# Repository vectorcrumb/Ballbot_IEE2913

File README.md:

# IEE2913
Codigo, esquematicos y planos para proyecto Ballbot para el ramo IEE2913, Diseño Electrico, semestre 2019-2

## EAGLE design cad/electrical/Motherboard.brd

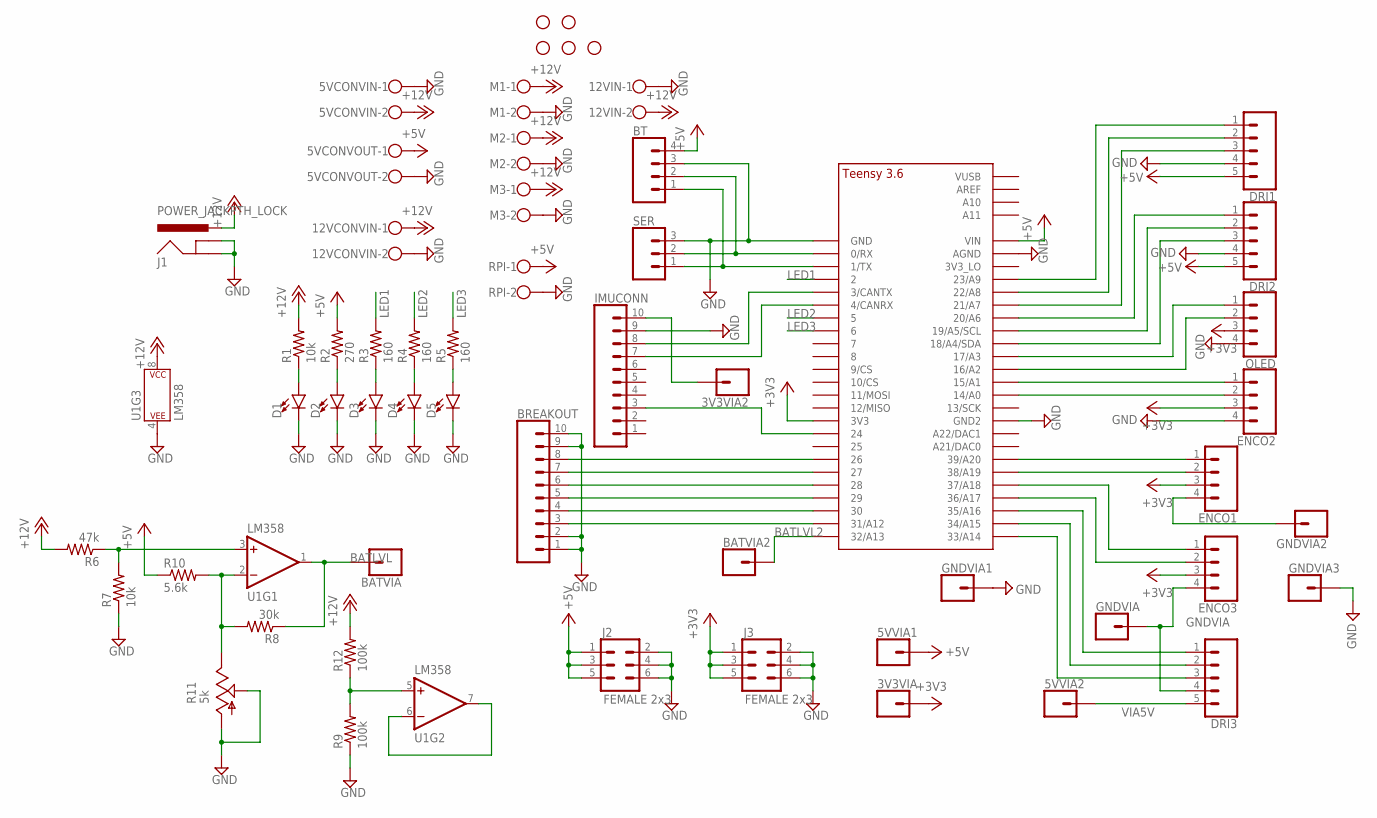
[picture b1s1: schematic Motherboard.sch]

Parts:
3V3VIA, 3V3VIA2, 5VVIA1, 5VVIA2: CONN_01; 1X01
5VCONVIN, 5VCONVOUT, 12VCONVIN, 12VIN: W237-102
BATVIA, BATVIA2: CONN_01; 1X01
BREAKOUT: CONN_10LOCK; 1X10_LOCK
BT: CONN_04LOCK; 1X04_LOCK
D1, D2, D3, D4, D5: LED5MM-KIT; LED_5MM-KIT
DRI1, DRI2, DRI3: CONN_05LOCK; 1X05_LOCK
ENCO1, ENCO2, ENCO3: CONN_04LOCK; 1X04_LOCK
GNDVIA, GNDVIA1, GNDVIA2, GNDVIA3: CONN_01; 1X01
H1, H2, H4, H5, H6: STAND-OFF
IMUCONN: CONN_10LOCK; 1X10_LOCK
J1: POWER_JACKPTH_LOCK; POWER_JACK_PTH_LOCK
J2, J3: FEMALE 2x3; 2X3
M1, M2, M3: W237-102
OLED: CONN_04LOCK; 1X04_LOCK
R1, R7: 10k; 0207/10
R2: 270; 0207/10
R3, R4, R5: 160; 0207/10
R6: 47k; 0207/10
R8: 30k; 0207/10
R9, R12: 100k; 0207/10
R10: 5.6k; 0207/10
R11: 5k; B25P
RPI: W237-102
SER: CONN_03LOCK; 1X03_LOCK
U1: LM358; DIP08
U$1: TEENSY_3.5/3.6_BASIC

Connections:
+3V3: 3V3VIA.1, ENCO1.3, ENCO2.3, ENCO3.3, J3.1, J3.3, J3.5, OLED.3, U$1.3V3
+5V: 5VCONVOUT.1, 5VVIA1.1, BT.4, DRI1.5, DRI2.5, J2.1, J2.3, J2.5, R2.2, R10.1, RPI.1, U$1.VIN
+12V: 5VCONVIN.2, 12VCONVIN.1, 12VIN.2, J1.PWR, M1.1, M2.1, M3.1, R1.2, R6.2, R12.2, U1.8 (P$V+)
BATLVL: BATVIA.1, R8.1, U1.1 (OUT)
BATLVL2: BATVIA2.1, U$1.32/A13
GND: 5VCONVIN.1, 5VCONVOUT.2, 12VCONVIN.2, 12VIN.1, BREAKOUT.1, BREAKOUT.2, BREAKOUT.9, BREAKOUT.10, BT.3, D1.K (C), D2.K (C), D3.K (C), D4.K (C), D5.K (C), DRI1.4, DRI2.4, ENCO2.4, GNDVIA1.1, GNDVIA3.1, IMUCONN.9, J1.GND, J1.GNDBREAK, J2.2, J2.4, J2.6, J3.2, J3.4, J3.6, M1.2, M2.2, M3.2, OLED.4, R7.1, R9.1, R11.A, R11.S, RPI.2, SER.3, U1.4 (P$V-), U$1.AGND, U$1.GND, U$1.GND2
GNDVIA: DRI3.4, ENCO3.4, GNDVIA.1
LED1: R3.2, U$1.2
LED2: R4.2, U$1.5
LED3: R5.2, U$1.6
unnamed: DRI1.1, U$1.23/A9
unnamed: DRI1.2, U$1.22/A8
unnamed: DRI1.3, U$1.21/A7
unnamed: DRI2.3, U$1.18/A4/SDA
unnamed: DRI2.2, U$1.19/A5/SCL
unnamed: DRI2.1, U$1.20/A6
unnamed: ENCO2.1, U$1.15/A1
unnamed: ENCO2.2, U$1.14/A0
unnamed: ENCO1.1, U$1.39/A20
unnamed: ENCO1.2, U$1.38/A19
unnamed: ENCO3.1, U$1.37/A18
unnamed: ENCO3.2, U$1.36/A17
unnamed: DRI3.1, U$1.35/A16
unnamed: DRI3.2, U$1.34/A15
unnamed: DRI3.3, U$1.33/A14
unnamed: BT.1, SER.1, U$1.1/TX
unnamed: BT.2, SER.2, U$1.0/RX
unnamed: IMUCONN.8, U$1.3/CANTX
unnamed: IMUCONN.7, U$1.4/CANRX
unnamed: IMUCONN.3, U$1.24
unnamed: R9.2, R12.1, U1.5 (+IN)
unnamed: BREAKOUT.3, U$1.31/A12
unnamed: BREAKOUT.4, U$1.30
unnamed: BREAKOUT.5, U$1.29
unnamed: BREAKOUT.6, U$1.28
unnamed: BREAKOUT.7, U$1.27
unnamed: BREAKOUT.8, U$1.26
unnamed: D2.A, R2.1
unnamed: D1.A, R1.1
unnamed: D3.A, R3.1
unnamed: D5.A, R5.1
unnamed: D4.A, R4.1
unnamed: 3V3VIA2.1, IMUCONN.10
unnamed: OLED.1, U$1.17/A3
unnamed: OLED.2, U$1.16/A2
unnamed: R6.1, R7.2, U1.3 (+IN)
unnamed: U1.6 (-IN), U1.7 (OUT)
unnamed: R8.2, R10.2, R11.E, U1.2 (-IN)
unnamed: ENCO1.4, GNDVIA2.1
VIA5V: 5VVIA2.1, DRI3.5

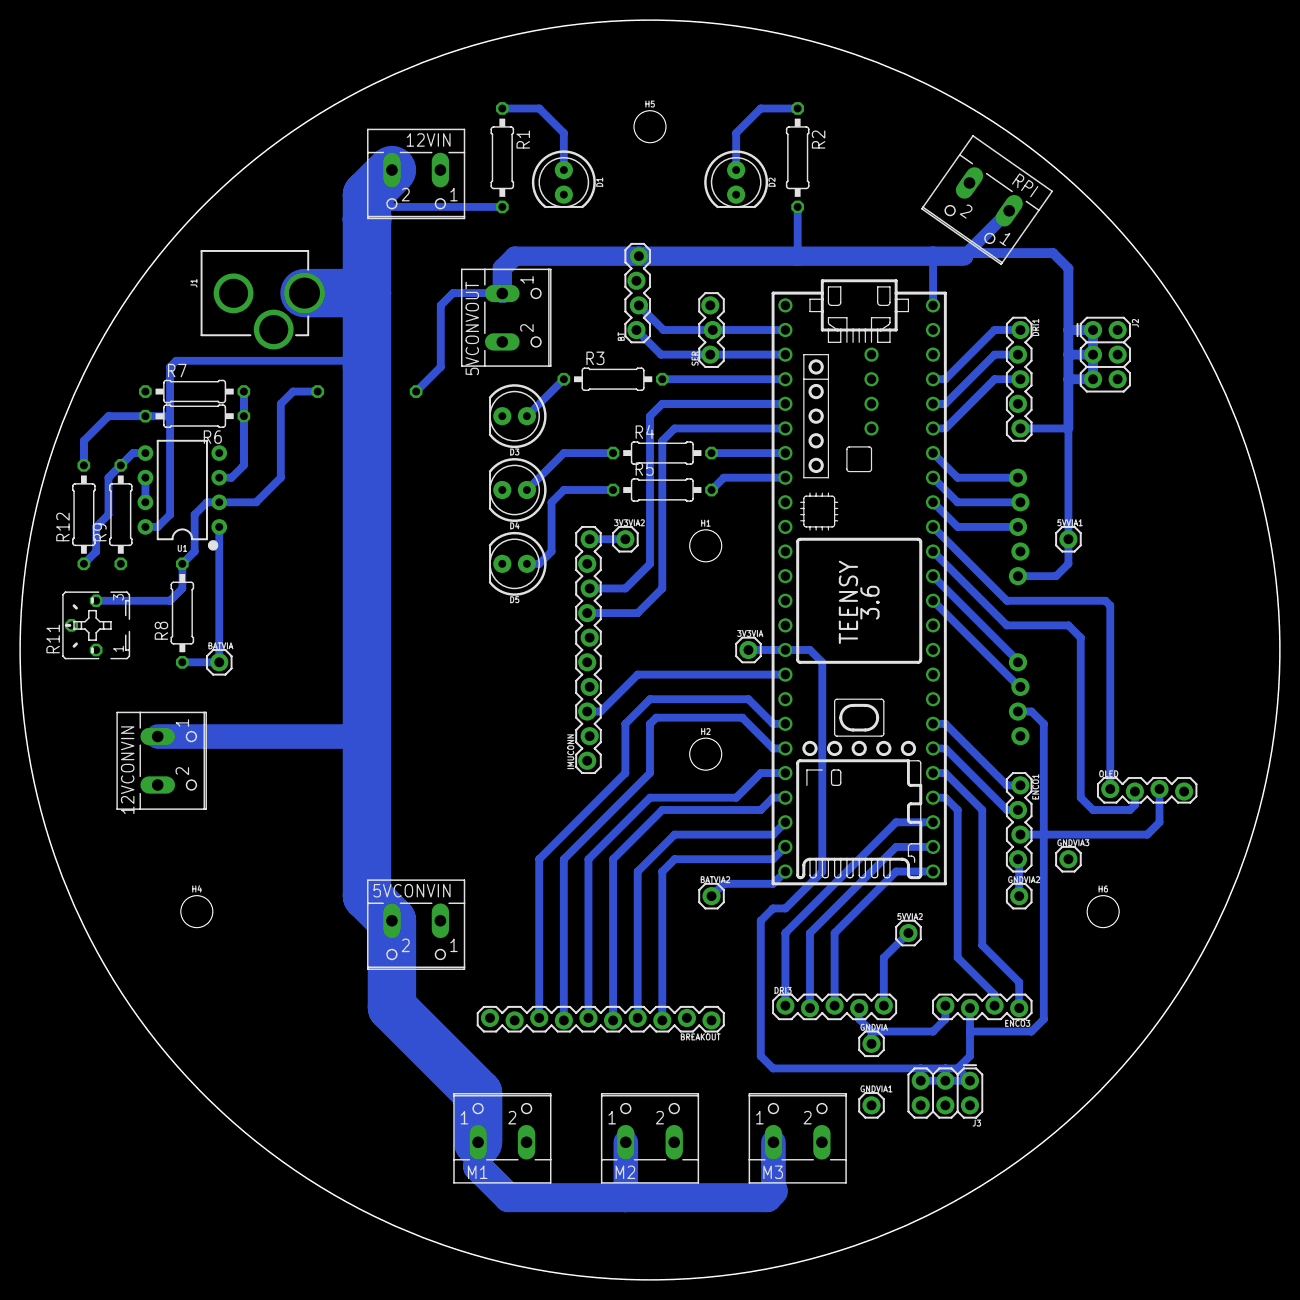
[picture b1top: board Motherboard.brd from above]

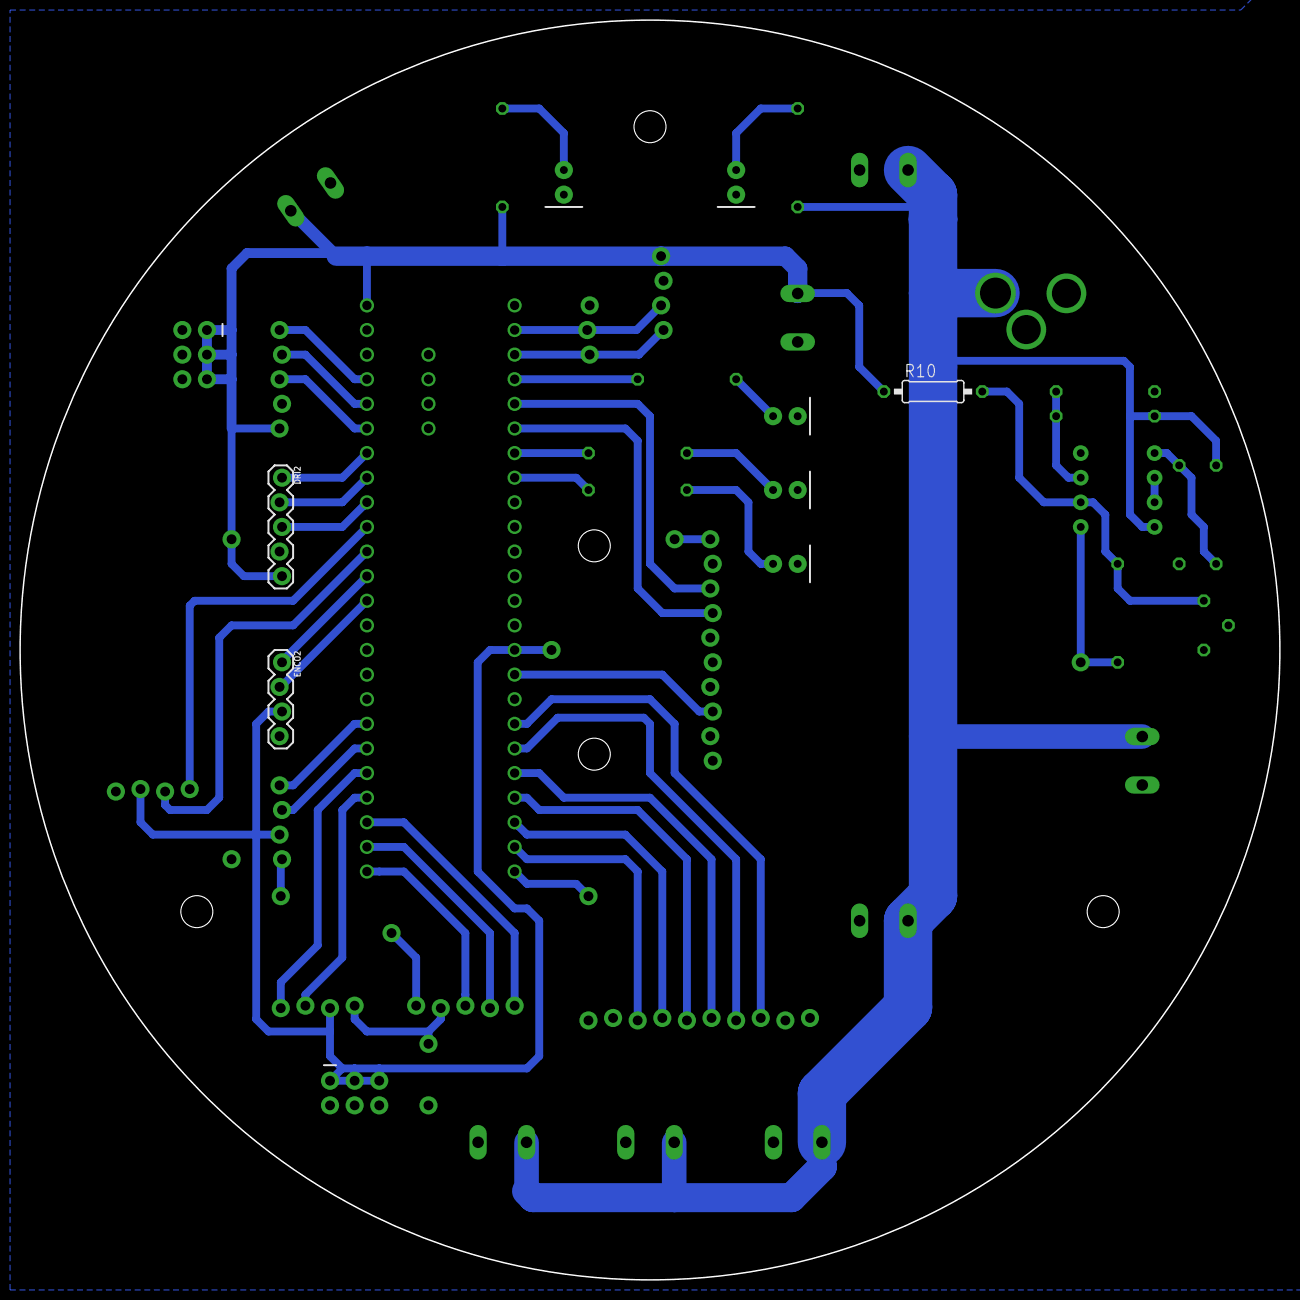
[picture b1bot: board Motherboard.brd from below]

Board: 2 copper layers, 130.0 x 130.0 mm, 56 parts (3 on the bottom side), 50 nets.

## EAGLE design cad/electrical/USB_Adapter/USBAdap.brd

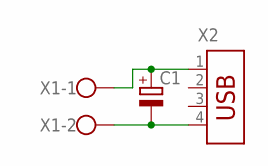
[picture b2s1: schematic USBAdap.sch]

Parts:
C1: CPOL-EUE5-8.5; E5-8,5
X1: W237-102
X2: USB-787616; USB

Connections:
unnamed: C1.+, X1.1, X2.1
unnamed: C1.-, X1.2, X2.4

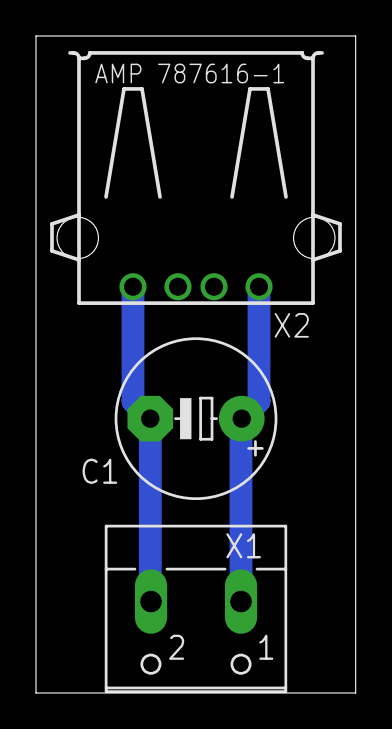
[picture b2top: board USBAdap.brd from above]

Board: 2 copper layers, 17.8 x 36.5 mm, 3 parts (0 on the bottom side), 2 nets.

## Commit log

2019-10-09 Added robot basic code and electrical CAD
2019-10-10 Imported robot code and electrical CAD
2019-10-11 Implemented MPU9250 w/Madgwick filter and OLED.
2019-10-12 Added more OLED funcionality. Modified pinout.
2019-10-12 Modded gitignore.
2019-10-12 Removed config files.
2019-10-12 Modded main, deleted makefile.
2019-10-12 Removed makefile commit, modded main.cpp.
2019-10-13 COdigo motores
2019-10-16 Added base web interface.
2019-11-03 Working plots on UI, added PJON lib, began refactoring
2019-11-03 Removed tracking on Makefile
2019-11-07 Complete robot code refactoring. Added TeensyDelay library. Still have to fix errors for TorqueMotor class.
2019-11-14 Added torque control motor.
2019-11-15 Fixed startup errors for rewrite.
2019-11-15 Fixing motor PID issues.
2019-11-15 Continued debugging. Found error in sensor reading
2019-12-03 Ultima entrega funcional
2019-12-03 Placed IMU in functions.
2019-12-03 PID lib
2019-12-04 Working PI not tuned
2019-12-09 PID tuning and torque sign
2019-12-11 11/Dic
2019-12-13 Nothing
2019-12-14 PID Torque funcionando.
2019-12-15 Reworked PID and stuff. Have to test.
2019-12-16 Fixed makefile
2019-12-16 Low pass filter
2019-12-17 Working current sensors. Motor PI wrong.
2019-12-17 Added eigen and moving average.
2019-12-18 LQR discrete constants
2019-12-18 Working PI controller on 3 motors.
2019-12-18 Reintegrated IMU. Variable offsets in readings.
2019-12-18 Added DMP library for test.
2019-12-18 Dropped DMP, added changes.
2019-12-18 Working IMU calibration
2019-12-19 Working robot code. Have to tune and add Kalman.
2019-12-19 Tuning LQR
2019-12-19 Version Presentacion Final.
2019-12-23 Working Kalman.
2022-06-21 Bump numpy from 1.16.4 to 1.22.0 in /code/app/web
    Bumps [numpy](https://github.com/numpy/numpy) from 1.16.4 to 1.22.0.
    - [Release notes](https://github.com/numpy/numpy/releases)
    - [Changelog](https://github.com/numpy/numpy/blob/main/doc/HOWTO_RELEASE.rst)
    - [Commits](https://github.com/numpy/numpy/compare/v1.16.4...v1.22.0)
    ---
    updated-dependencies:
2023-05-01 Bump flask from 1.0.2 to 2.3.2 in /code/app/web
    Bumps [flask](https://github.com/pallets/flask) from 1.0.2 to 2.3.2.
    - [Release notes](https://github.com/pallets/flask/releases)
    - [Changelog](https://github.com/pallets/flask/blob/main/CHANGES.rst)
    - [Commits](https://github.com/pallets/flask/compare/1.0.2...2.3.2)
    ---
    updated-dependencies:

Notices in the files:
parts and their libraries:
SparkFun-Hardware: Licensing: Creative Commons ShareAlike 4.0 International - https://creativecommons.org/licenses/by-sa/4.0
